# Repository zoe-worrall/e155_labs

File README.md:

# e155_labs
A repository of all of the labs Zoe made at Harvey Mudd College for Microprocessors (E155)

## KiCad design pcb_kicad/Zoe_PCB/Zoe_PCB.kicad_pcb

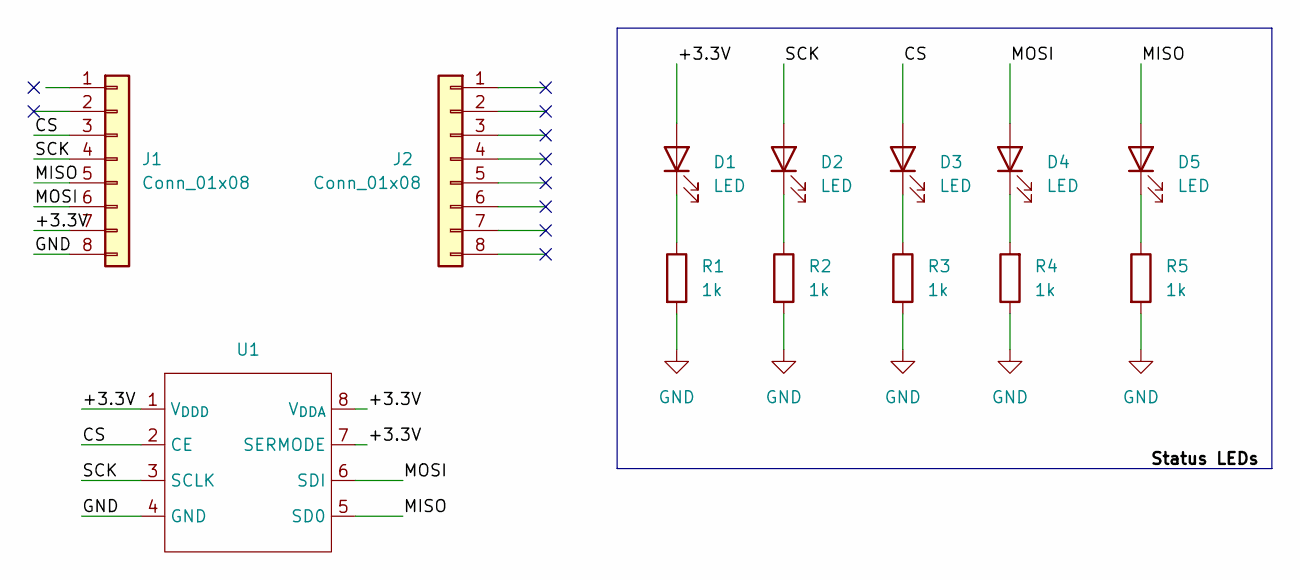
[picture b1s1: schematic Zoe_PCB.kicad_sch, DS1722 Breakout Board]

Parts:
D1, D2, D3, D4, D5: LED; LED_0805_2012Metric
J1, J2: Conn_01x08; PinHeader_1x08_P2.54mm_Vertical
R1, R2, R3, R4, R5: 1k; R_0805_2012Metric
U1: Zoe_DS1722

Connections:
/+3.3V: D1.2 (A), J1.7, U1.1 (V_{DDD}), U1.7 (SERMODE), U1.8 (V_{DDA})
/CS: D3.2 (A), J1.3, U1.2 (CE)
/MISO: D5.2 (A), J1.5, U1.5 (SD0)
/MOSI: D4.2 (A), J1.6, U1.6 (SDI)
/SCK: D2.2 (A), J1.4, U1.3 (SCLK)
GND: J1.8, R1.2, R2.2, R3.2, R4.1, R5.2, U1.4 (GND)
unnamed: D1.1 (K), R1.1
unnamed: D2.1 (K), R2.1
unnamed: D3.1 (K), R3.1
unnamed: D4.1 (K), R4.2
unnamed: D5.1 (K), R5.1

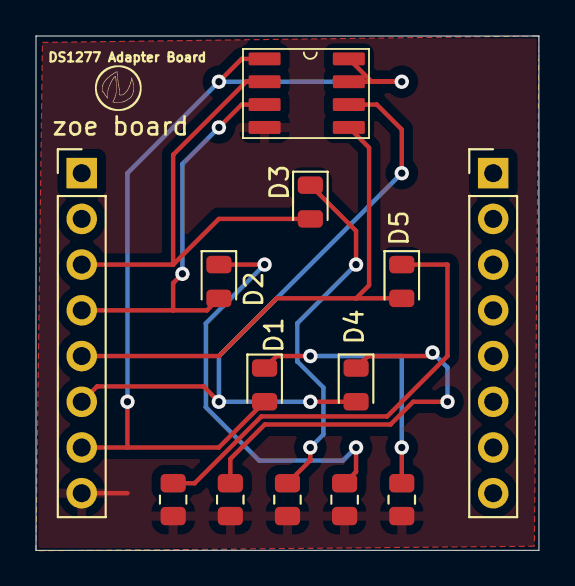
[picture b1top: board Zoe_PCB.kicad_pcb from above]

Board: 2 copper layers, 27.9 x 28.6 mm, 13 parts (0 on the bottom side), 11 nets.

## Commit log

2024-08-29 Create README.md
    Made a base README folder
2024-08-29 Initial Commit of all new files for the git repository as well as the mcu, fpga, and all other boards
2024-08-29 Trying to fix initial issue: I believe it was because README was in two places. Deleted the one that I hadn't written personally
2024-08-29 Fixing adds and commits. Hopefully can push origin into repo now
2024-08-29 Initialising gh-pages branch according to https://quarto.org/docs/publishing/github-pages.html\#publish-command
2024-08-29 Published gh-pages. Added a publish action that will run whenever main starts
2024-08-29 Added all Quarto Portfolio items into the github page. Previously had it backwards: cloned a repo, made a portfolio. I needed to get out of the cloned repo
2024-08-29 Built site for gh-pages
2024-08-29 Moved files around to new locations to allow for correct file structure in E155 checkoff
2024-08-29 Edited _quarto file to contain links for both e-155 website and blog
2024-08-29 Changed font size in some places. Trying to figure out how to change navbar for e-155
2024-08-30 Moved files around and decided on final layout. Fixed the large size of the navigation bar
2024-08-30 Added profile pic, listings for both Blog and Labs, and (for now) removed my personal .css file (was preventing scrolling)
2024-08-30 Fine tuned the Lab pages and nav bar. Added linked in at bottom
2024-08-30 Added headers to all labs. Added a new blog post with goals, because I wasn't sure about E155 specs
2024-08-30 Added the categories back into the Blog. Confirmed that all parts of Quarto Portfolio Specs are met
2024-08-31 Was able to figure out a ST-Link issue. Currently programming LEDs for board; having trouble uploading FPGA design. Will need to retry demo.
2024-09-01 created file for projects and labs
2024-09-01 Changed out lab01 with the current lab01 version I have working on my board. Still need to add testbench
2024-09-02 Finally got all test benches working on board. Can run all code for controlling leds and 7-segment from FPGA. Pin 10 on the board appears to be shorted to 3.3V somewhere
2024-09-02 Made README into an actual *.md file
2024-09-02 Added header to README.md
2024-09-02 Adjusted the seven segment display so that 0 starts at 0, not 1, and adjusted testbench accordingly
2024-09-02 Removed copy of README file
2024-09-02 Trying to improve readability of README
2024-09-02 Indented tree by 1 to improve readability of README
2024-09-02 Added link to Module 1
2024-09-03 Added all additional files, including those missing github files
2024-09-03 Added in teh variables that had been randomly ignored -- unsure why .git ignore was being applied to the .sv files
2024-09-06 Added a new blog post and modified some of my labs with an updated schematic
2024-09-06 removed prof brake comment
2024-09-06 Change photo of blog post
2024-09-06 A few minor edits to the blog post again
2024-09-07 Added files and updated quarto page
2024-09-07 Add all of lab2 + comments
2024-09-09 Updating all of the files and website projects for this website
2024-09-10 Published blog post, added images
2024-09-10 Changed image for Post 3
2024-09-17 Added working verison of lab03 to the class
2024-09-17 Trying to make sure all folders are in github
2024-09-17 Hopefully adding all folders
2024-09-17 Added changes to my website and lab 3
2024-09-17 Added new images so that they were more accurate
2024-09-17 Added my blog post
2024-09-17 Finished bullet point listing
2024-09-19 Updated website with some new lines about test benches and how they work to prove that my system is functioning
2024-09-19 Updated block and schematic diagrams for checkoff
2024-09-19 Depressing table orientation
2024-09-19 Added next_state column
2024-09-19 Added new working (completely) code to the github
2024-09-24 was able to control frequency of LED using TIM2
2024-09-25 Completed the classes and got the speaker working
2024-09-26 Updated all C files with comments
2024-09-26 Mistakes were made, but we've fixed them (hopefully)
2024-09-26 Changed schematic
2024-09-26 removed *.MOV commits
    Worked with prof brake to remove the *.MOV file that would potentialy break everything
2024-09-26 changed video file to link
    Made it so that the video points to a youtube video and isn't trying to upload a large image file to github.
2024-09-26 .gitignore should now be working (https://stackoverflow.com/questions/1139762/ignore-files-that-have-already-been-committed-to-a-git-repository)
2024-09-26 Created lab4_schematic
    Set up lab4 schematic: hopefully nothing else is broken now :)
2024-09-26 .gitignore should now be working (prev removed _site, now I'm also removing the .quarto) (https://stackoverflow.com/questions/1139762/ignore-files-that-have-already-been-committed-to-a-git-repository)
2024-09-26 Updated .gitignore
    Removing private things (like keys)
2024-09-29 Added Base for Lab
    Finished getting the basics for the lab setup- currently facing issues with folders internally.
2024-10-01 Got button lighting up
    Finished the intro to interrupts for the button program. Can now interrupt using PA5, and send trigger to PB3
2024-10-01 Started kicad
    Began the intro to kicad video while following along with lesson plan for PCB. Made working library,
2024-10-01 Updated the breakout board
    updated PCB with some relabeling
2024-10-01 Added new DS1722 Footprint
    Created new footprint for the DS1722
2024-10-01 Saving PCB Diagram :D
    Please don't erase it this time
2024-10-01 Added a blog post
    Added another "The Swamp that Stands Between" post.
2024-10-01 Posts on background
    Adjusted the the blogpost category and the date of publishing for posts 4 and 5.
2024-10-03 Updated the interrupt code
    Currently able to detect motor interrupts, but not able to log the counter values for frequency.
    Uses pins PA5 and PA9.
2024-10-03 Changed logic in main
    Changed the way idx is defined in main so that it a. uses a variable to tell if the array has been filled and b. Calculates frequency directly (was originally doing integer division, so frequency end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
2024-10-03 Finished PCB board and confirmed readouts of motor
    Finished programming PCB chip, also started checking the frequency of the motor in lab, and it appears to be correct :) -- need to add additional algorithms for excellence.
2024-10-08 Added To Lab5 and Finished Art Project
    Added additional files to the art project and updated my compiler so that it could print.
2024-10-08 Added blog post
    added a blog post - I'll add one later today too
2024-10-08 Updated my lab5 project
    Added descriptions to the button_interrupt code in my lab5
2024-10-10 Updated Hz to be rev/sec
    Updated the main.c program for Lab 5 so that it shows revolutions per second, not Hz.
2024-10-10 Created RF Circuitry page.
    Added RF Circuitry page and uploaded current python notebook.
2024-10-10 Added to index
    incorporated the index into the rf so it hopefully shows on the website
2024-10-10 Updated _quarto
    Made it so that RF was included in drop downs.
2024-10-10 Gerber File 3 Uploaded
    Uploaded a different gerber file after making sure that it had drill turned on
2024-10-12 Updated RF Circuit Webpage
    Added and edited ipynb files that can be used as supplementary for Design Project 1
2024-10-12 Added a new blog post
    Added new blog post, updated an old one. Want to try putting my RF writeup in the RF folder via Quarto, as well, but that will take time with the photos.
2024-10-16 Updated Lab6 Code
    Worked a bit on SPI data and lab 6. Also looking ahead at Lab 7. Currently unsure if some variables in my code should be volatile or not, but unable to check until the chips are brought into the lab.
2024-10-19 Updated SPI Program
    Ft. Xavier the GOAT, realised that I wasn't toggling my chip select, and was able to confirm that I was sending data using Pin PA12 on my MCU's SPI
2024-10-21 Finally got it working!
    Can successfully send and receive USART, as well as print out the temperature using SPI from my board.
2024-10-22 Working on Lab6 and MCU
    Working on Lab 6, and also updated the SPI function
2024-10-22 Finished Lab 6 Writeup
    completed writeup for lab 6, and uploaded a video of the system working (made by connecting my iPad to the ESP8266 connection)
2024-10-22 Lab 6 Updated
    It actually didn't work in github page uploading because i didn't put an image in, so hopefully this works now
2024-10-22 lab 6 update
    updated photo
2024-10-22 New Blog Post
    Epic the Musical and passion blog post
2024-10-22 removed photo from blog
2024-11-01 Updated fpga encoding tutorial
    Lab 7 meant that I had to retroactively relearn all of the fpga things - glad I made the guide, but it glossed over some things, so I added a short sentence at the end for future users.
2024-11-02 Updated website stuff
    Added new post
2024-11-06 Finally got the program working
    It took ages to realize that the problem was not, in fact, my code, but my board. I finally used someone else's board with my old code just to double check, and saw that the past 96 hours of programm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
2024-11-06 Updated a few lines in writeup
    Will continue the writeup after completing RF Writeup tomorrow.
2024-11-09 Added new labs and Radio Freq Files
    Updated website with current radio frequency file
2024-11-13 Updated current Github
    Updated Lab 7 for MicroP's, added additional plots for the Python File
2024-11-21 UPdated clocks and Radio Frequency
    Updated data
2024-11-21 Updated RF Index
    made it link to lab5 code
2024-11-22 Updated my RF board
    Updated things
2024-12-07 Updated Lab6
    Updated Lab 6 with new code
2024-12-07 updated so that lab6 is included
    updated to inlcude the python snippet for lab6
2024-12-14 Added Stuff for RF
    Added RF files for updating my DP2
2024-12-14 Updated index.qmd
    Updated index.qmd to now include DP2 in the browser
2024-12-14 Updated Blogs
    Finally pushed all the blogs to my website

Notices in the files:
pcb_kicad/Zoe_PCB/Zoe_PCB.kicad_sch:
creativecommons.org/licenses/by/4.0
License: CC by 4.0
